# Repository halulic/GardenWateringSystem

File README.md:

Overview

This project is an automatic plant watering system based on ESP32.
It monitors soil moisture, temperature, and humidity and controls a water valve or pump to keep the soil moisture at a defined target level.

The system uses a TFT display for real-time monitoring and allows simple configuration of watering parameters.

⸻

Main Features
	•	Automatic watering based on soil moisture
	•	ESP32 microcontroller
	•	TFT display interface
	•	Real-time monitoring of:
	•	Soil moisture
	•	Temperature
	•	Humidity
	•	Adjustable target moisture level
	•	MOSFET-controlled water valve or pump
	•	Clear visual status indicators on the display

⸻

Hardware

Main components used:
	•	ESP32 development board
	•	Soil moisture sensor
	•	SHT41 temperature & humidity sensor
	•	DS3231 RTC
	•	4.0” TFT display (ILI9488)
	•	MOSFET driver (AO3400)
	•	Water valve or pump
	•	24V power supply (for valves)

⸻

Display Information

The TFT display shows:
	•	Soil moisture percentage
	•	Temperature
	•	Humidity
	•	Target moisture level
	•	Valve status
	•	System status indicators

⸻

Applications
	•	Indoor plant watering
	•	Greenhouse automation
	•	Garden irrigation control
	•	Experimental ESP32 automation projects

⸻

Future Improvements

Planned upgrades include:
	•	WiFi monitoring
	•	Data logging
	•	Mobile notifications
	•	Multi-zone watering control

⸻

License

Open-source project for educational and DIY use.

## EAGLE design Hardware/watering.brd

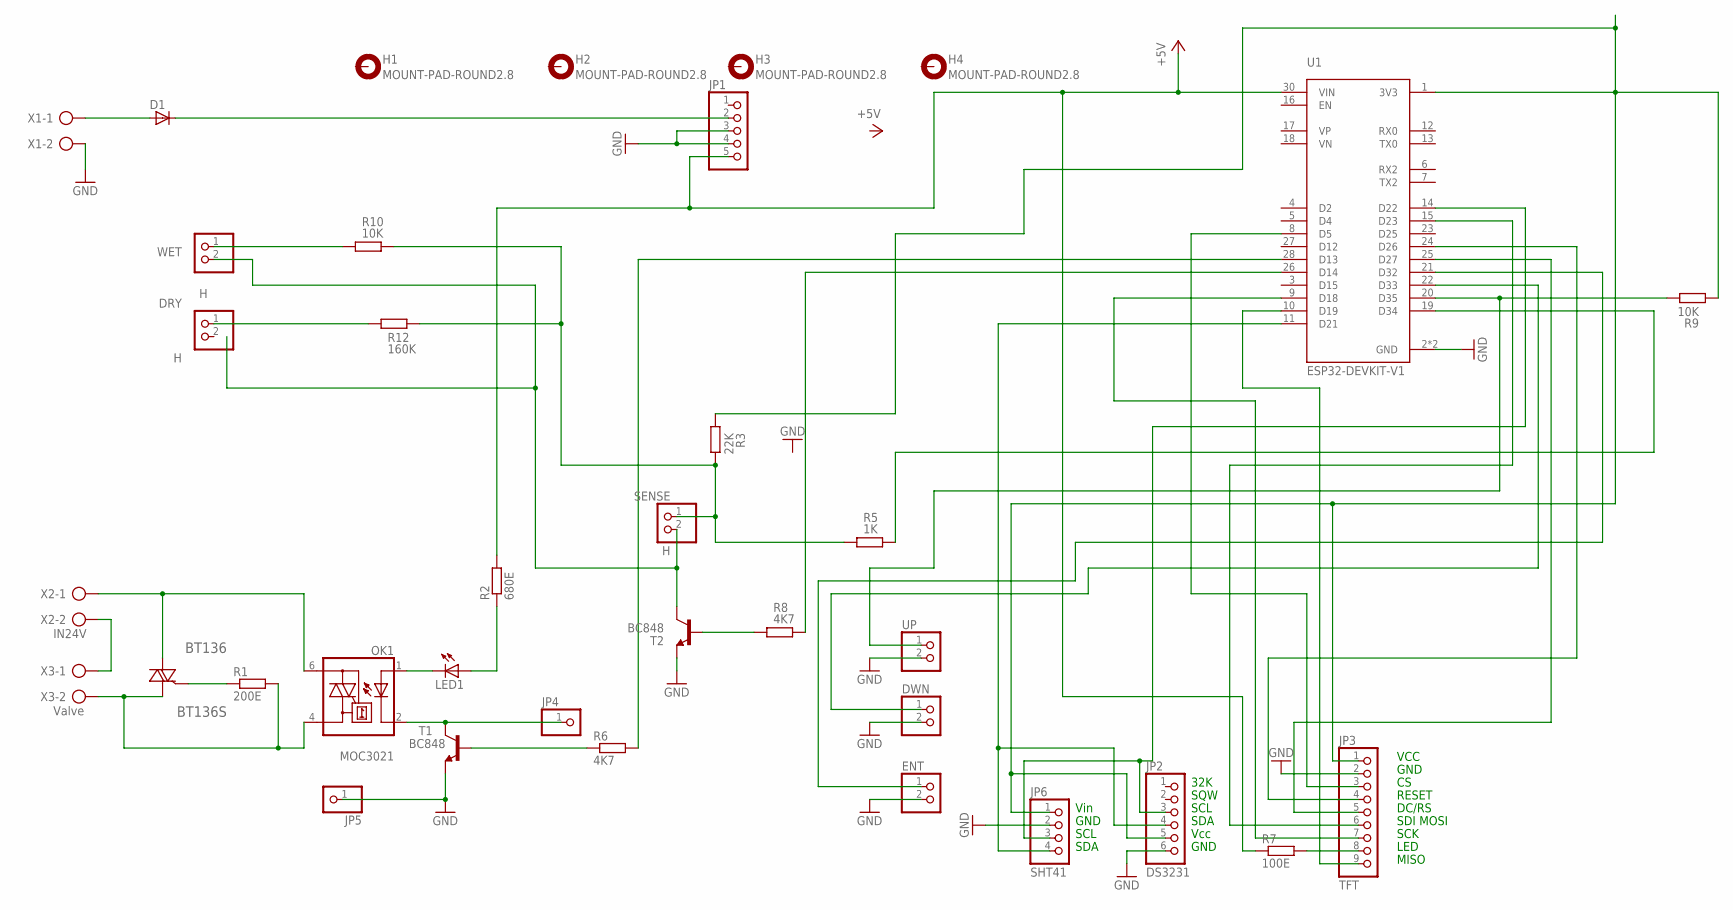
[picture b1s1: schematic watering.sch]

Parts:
BT136: BT136S; DPAK228P987X240-3N
D1: D-SOD-80; SOD80
DRY: H; 1X02
DWN: PINHD-1X2; 1X02
ENT: PINHD-1X2; 1X02
H1, H2, H3, H4: MOUNT-PAD-ROUND2.8; 2,8-PAD
JP1: PINHD-1X5; 1X05
JP2: DS3231; 1X06
JP3: TFT; 1X09
JP4, JP5: PINHD-1X1; 1X01
JP6: SHT41; 1X04
LED1: LEDCHIPLED_0805; CHIPLED_0805
OK1: MOC3021; DIL6-SMD
R1: 200E; R0603
R2: 680E; R0603
R3: 22K; R0603
R5: 1K; R0603
R6, R8: 4K7; R0603
R7: 100E; R0603
R9, R10: 10K; R0603
R12: 160K; R0603
SENSE: H; 1X02
T1, T2: BC848; SOT23
U1: ESP32-DEVKIT-V1; MODULE_ESP32_DEVKIT_V1
UP: PINHD-1X2; 1X02
WET: H; 1X02
X1: AK300/2
X2: IN24V; AK300/2
X3: Valve; AK300/2

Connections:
+5V: JP1.5, R2.2, R7.1, U1.30 (VIN)
GND: DWN.2, ENT.2, JP1.3, JP1.4, JP2.6, JP3.2, JP5.1, JP6.2, T1.2 (E), T2.2 (E), U1.2 (GND), U1.29 (GND), UP.2, X1.2
unnamed: X2.2, X3.1
unnamed: BT136.1 (A1), OK1.4 (A1), R1.2, X3.2
unnamed: BT136.3 (A2), OK1.6 (A2), X2.1
unnamed: JP2.5, JP3.1, JP6.1, R3.1, R9.1, U1.1 (3V3)
unnamed: BT136.2 (G), R1.1
unnamed: LED1.A, R2.1
unnamed: JP4.1, OK1.2 (C), T1.3 (C)
unnamed: LED1.C, OK1.1 (A)
unnamed: D1.2 (A), X1.1
unnamed: D1.1 (C), JP1.2
unnamed: R3.2, R5.1, R10.2, R12.2, SENSE.1
unnamed: DRY.1, R12.1
unnamed: R6.1, T1.1 (B)
unnamed: JP3.8, R7.2
unnamed: SENSE.2, T2.3 (C), WET.2
unnamed: R8.1, T2.1 (B)
unnamed: R10.1, WET.1
unnamed: JP2.3, JP6.3, U1.14 (D22)
unnamed: JP2.4, JP6.4, U1.11 (D21)
unnamed: JP3.7, U1.9 (D18)
unnamed: R8.2, U1.26 (D14)
unnamed: JP3.6, U1.15 (D23)
unnamed: R9.2, U1.20 (D35), UP.1
unnamed: JP3.3, U1.8 (D5)
unnamed: JP3.5, U1.25 (D27)
unnamed: JP3.4, U1.24 (D26)
unnamed: JP3.9, U1.10 (D19)
unnamed: DWN.1, U1.22 (D33)
unnamed: ENT.1, U1.21 (D32)
unnamed: R6.2, U1.28 (D13)
unnamed: R5.2, U1.19 (D34)

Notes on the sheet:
VCC
GND
RESET
DC/RS
SDI MOSI
SCK
LED
MISO
32K
SQW
SCL
SDA
Vcc
Vin

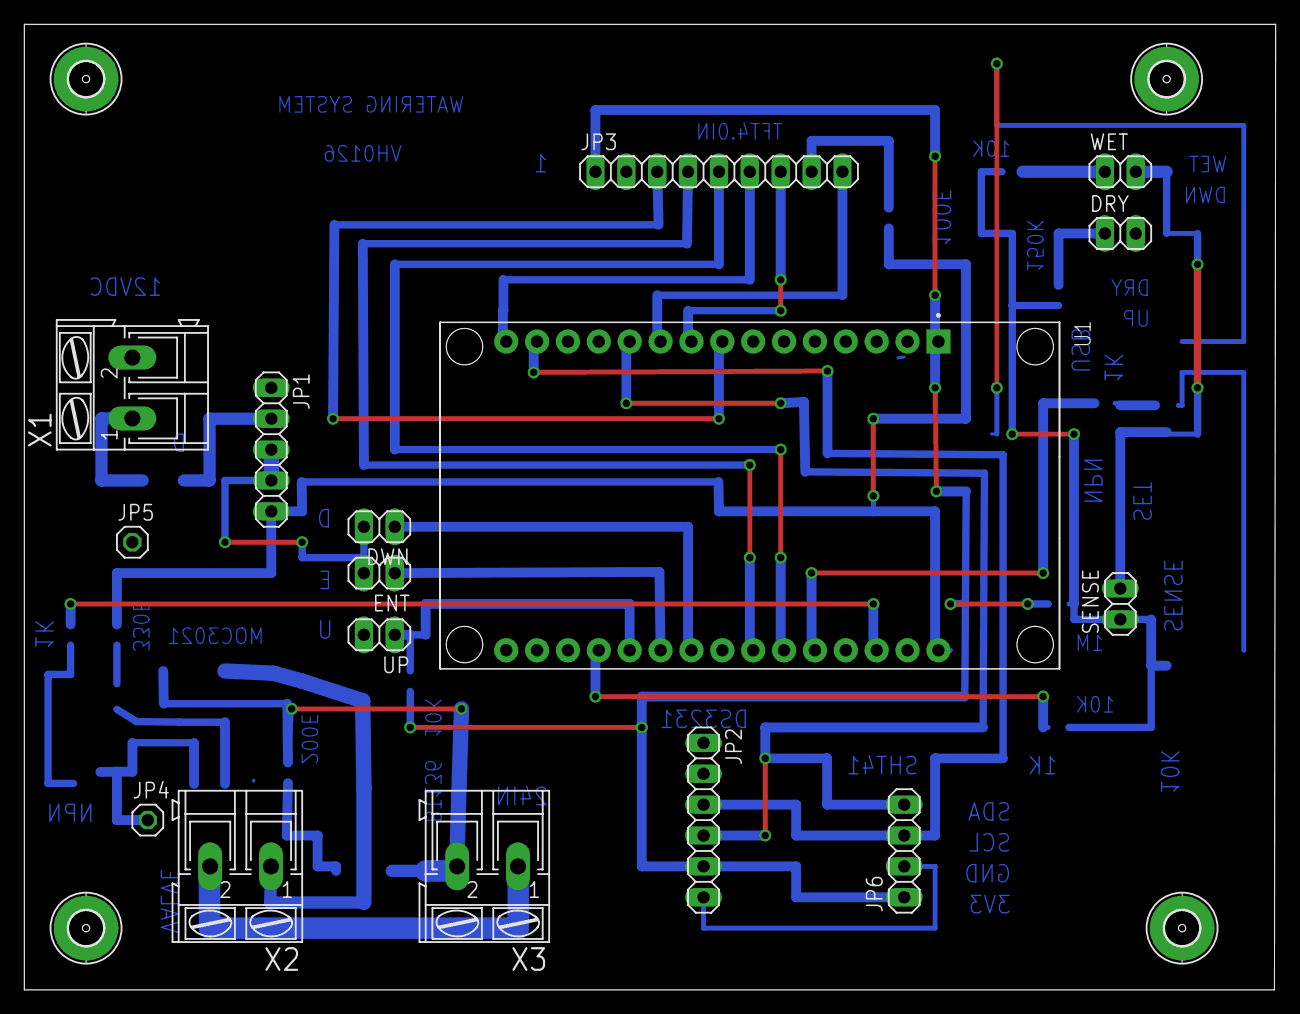
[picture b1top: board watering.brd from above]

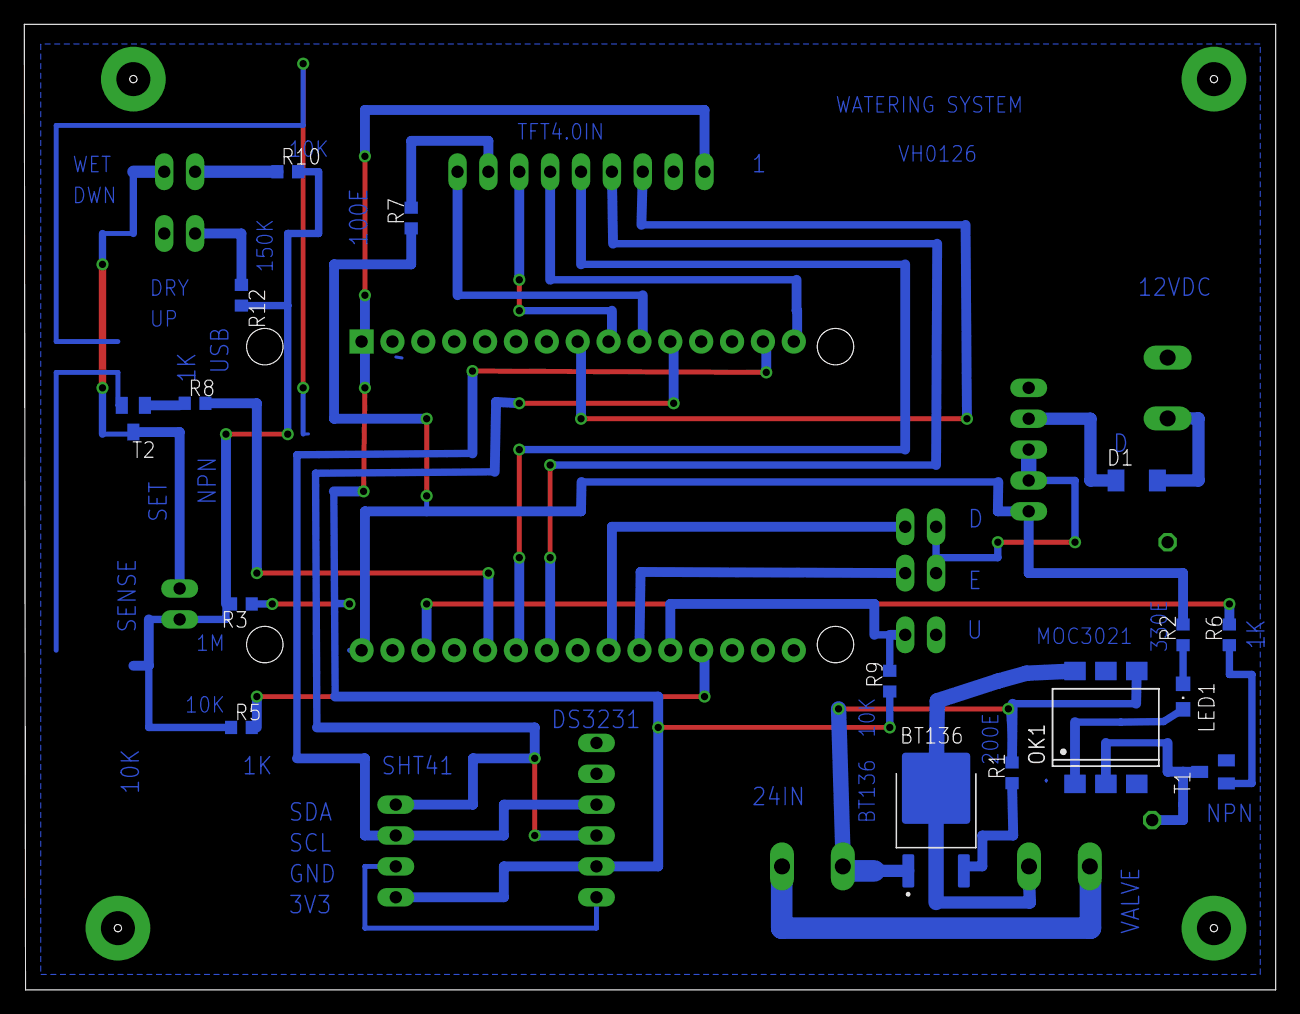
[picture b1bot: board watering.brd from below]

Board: 2 copper layers, 103.0 x 79.4 mm, 36 parts (16 on the bottom side), 33 nets.

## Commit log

2026-03-12 Add project overview and details to README
    This README outlines the features, hardware components, display information, applications, and future improvements of the automatic plant watering system project.
